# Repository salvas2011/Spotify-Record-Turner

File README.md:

#  RFID Record Player — ESP32-S3

> A modern record player that uses RFID-tagged vinyl coasters to control Spotify playback, powered by an ESP32-S3 and a custom PCB.

---

## How it works

Place a tagged vinyl coaster on the platter. The RFID reader identifies the tag, looks up the mapped Spotify URI, and starts playback. A Hall effect sensor detects when the platter is spinning — remove the record and the music pauses automatically. A stepper motor keeps the platter spinning for the full vinyl experience.

---

## PCB

<p align="center">
  
  &nbsp;
  
</p>

<p align="center">
  <em>Left: KiCad schematic &nbsp;·&nbsp; Right: PCB layout</em>
</p>

---

## Components

| Component | Purpose |
|---|---|
| ESP32-S3-DEV-KIT-N8R8 | Main microcontroller, Wi-Fi |
| RC522 RFID Reader | Reads RFID/NFC tags |
| 28BYJ-48 + ULN2003 | Stepper motor for spinning platter |
| A3144 Hall Effect Sensor | Detects platter rotation |
| NTAG213 NFC Tags | Attached to vinyl coasters |

---

## Wiring

### RC522 RFID (SPI)

| ESP32 GPIO | RC522 Pin |
|---|---|
| GPIO11 | MOSI |
| GPIO13 | MISO |
| GPIO12 | SCK |
| GPIO10 | CS (SDA) |
| GPIO9 | RST |
| 3.3V | 3.3V |
| GND | GND |

### ULN2003 Stepper Motor

| ESP32 GPIO | ULN2003 Pin |
|---|---|
| GPIO4 | IN1 |
| GPIO5 | IN2 |
| GPIO6 | IN3 |
| GPIO7 | IN4 |
| 5V (external) | VCC |
| GND | GND |

### A3144 Hall Effect Sensor

| ESP32 GPIO | Sensor Pin |
|---|---|
| GPIO38 | OUT |
| 3.3V | VCC |
| GND | GND |

### Power

5V 2A via barrel jack wired directly to the ESP32-S3 5V and GND pins.

---

## Pin notes

- GPIO35, 36, 37 are reserved internally on the N8R8 variant (Octal PSRAM) — do not use
- GPIO0 and GPIO46 are strapping pins — avoid for general use
- GPIO19/20 are USB D-/D+ — avoid if using native USB

---

## License

MIT

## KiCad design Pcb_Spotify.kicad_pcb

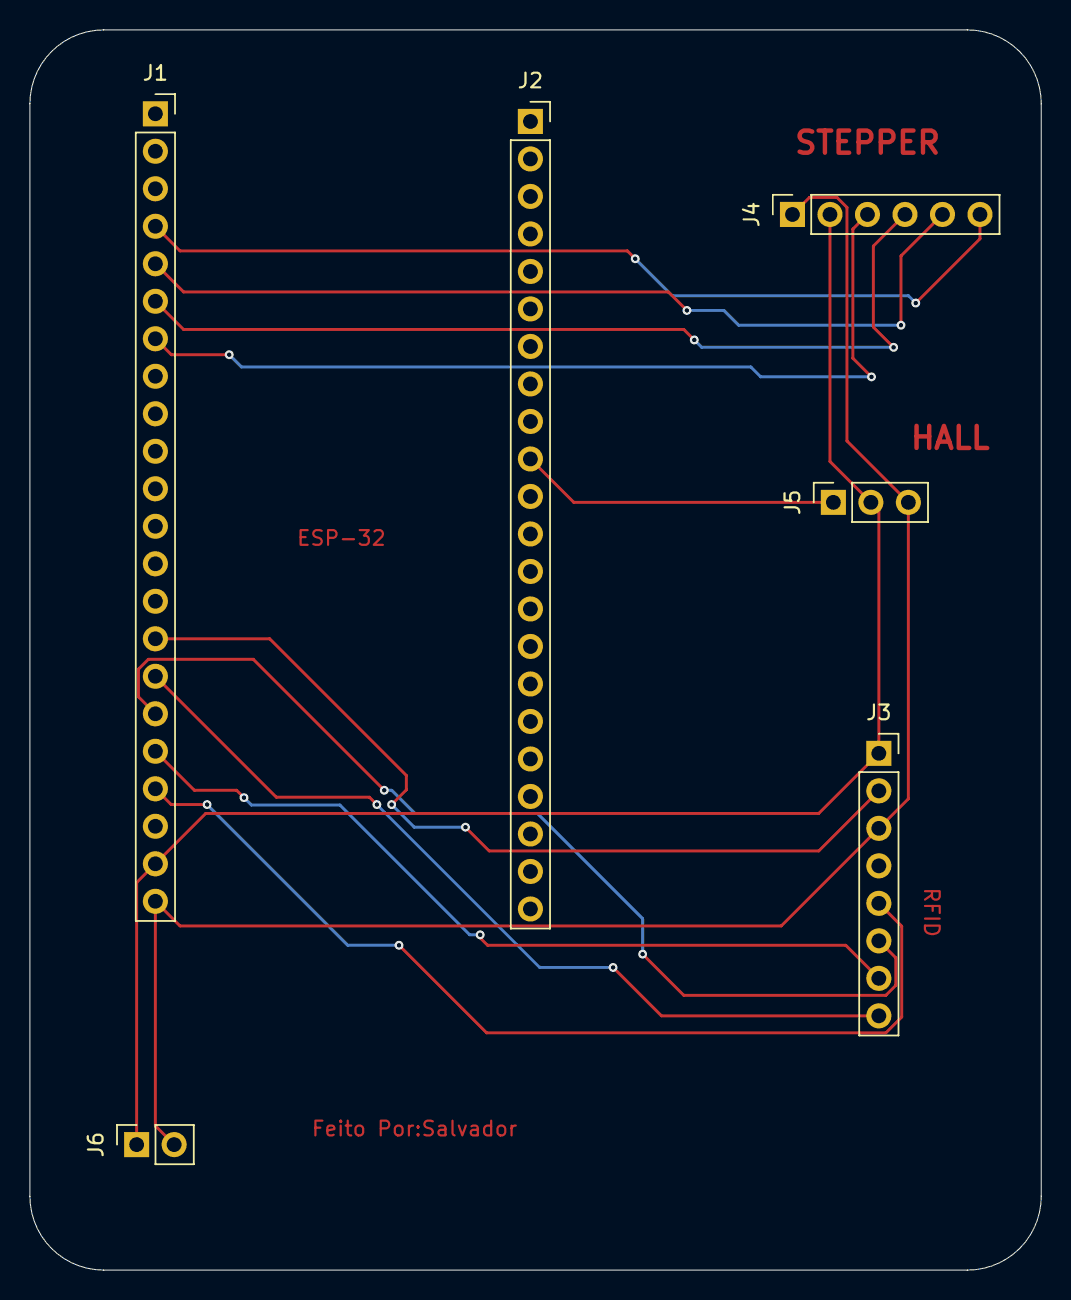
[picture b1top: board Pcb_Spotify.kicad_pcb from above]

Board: 2 copper layers, 68.5 x 84.0 mm, 6 parts (0 on the bottom side), 12 nets.

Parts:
J1, J2: Conn_01x22; PinSocket_1x22_P2.54mm_Vertical
J3: Conn_01x08; PinSocket_1x08_P2.54mm_Vertical
J4: Stepper; PinSocket_1x06_P2.54mm_Vertical
J5: Hall; PinSocket_1x03_P2.54mm_Vertical
J6: Input; PinSocket_1x02_P2.54mm_Vertical

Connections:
+5V: J1.21, J3.1, J4.2, J5.2, J6.1
GND: J1.22, J3.3, J4.1, J5.3, J6.2
unnamed: J1.4, J4.6
unnamed: J1.5, J4.5
unnamed: J1.6, J4.4
unnamed: J1.7, J4.3
unnamed: J1.15, J3.2
unnamed: J1.16, J3.8
unnamed: J1.17, J3.6
unnamed: J1.18, J3.7
unnamed: J1.19, J3.5
unnamed: J2.10 (Pin_10_10), J5.1

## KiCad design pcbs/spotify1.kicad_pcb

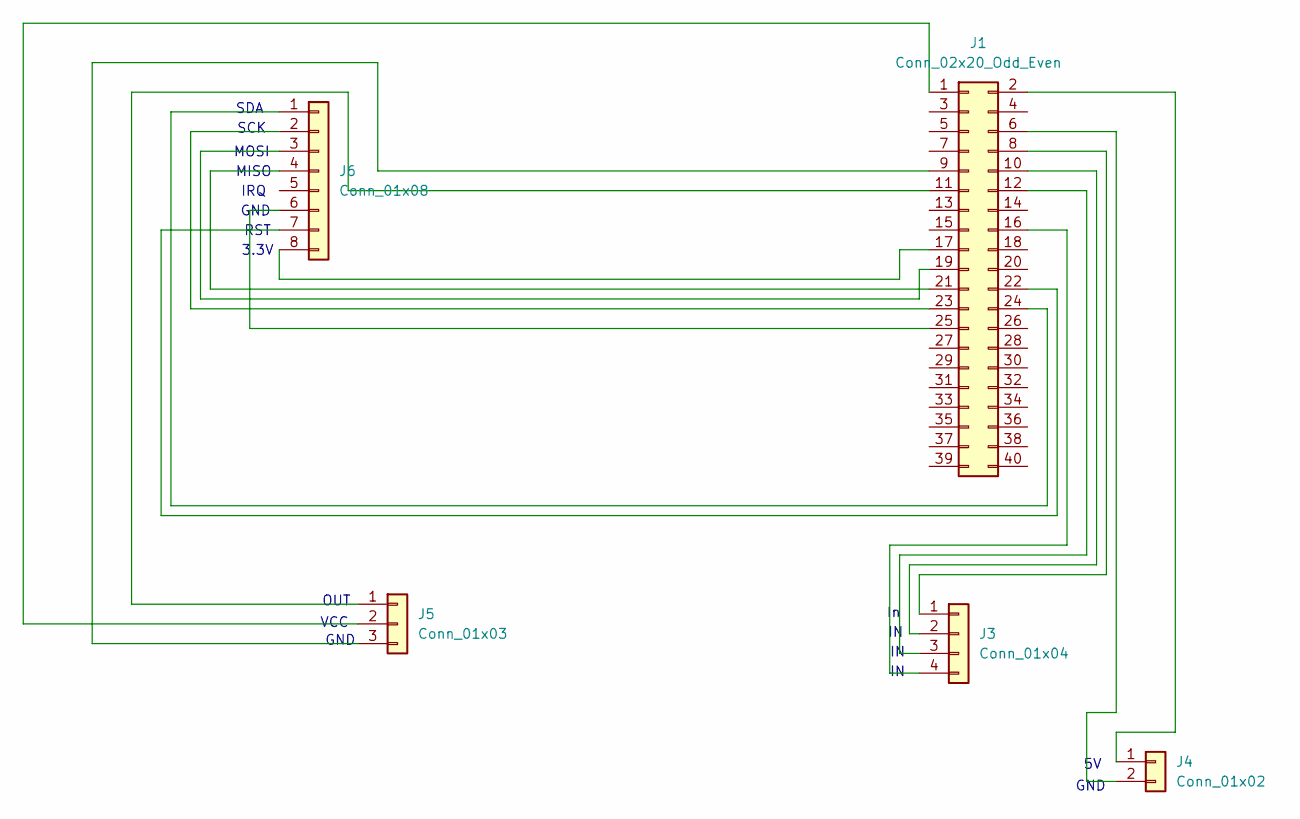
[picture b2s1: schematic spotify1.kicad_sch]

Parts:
J1: Conn_02x20_Odd_Even; PinSocket_2x20_P2.54mm_Vertical
J3: Conn_01x04; PinSocket_1x04_P2.54mm_Vertical
J4: Conn_01x02; PinSocket_1x02_P2.54mm_Vertical
J5: Conn_01x03; PinSocket_1x03_P2.54mm_Vertical
J6: Conn_01x08; PinSocket_1x08_P2.54mm_Vertical

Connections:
unnamed: J1.1, J5.2
unnamed: J1.2, J4.1
unnamed: J1.6, J4.2
unnamed: J1.8, J3.1
unnamed: J1.9, J5.3
unnamed: J1.10, J3.2
unnamed: J1.11, J5.1
unnamed: J1.12, J3.3
unnamed: J1.16, J3.4
unnamed: J1.17, J6.8
unnamed: J1.19, J6.3
unnamed: J1.21, J6.4
unnamed: J1.22, J6.7
unnamed: J1.23, J6.2
unnamed: J1.24, J6.1
unnamed: J1.25, J6.6

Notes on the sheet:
3.3V
IRQ
MISO
SCK
RST
MOSI
SDA
GND
VCC
OUT

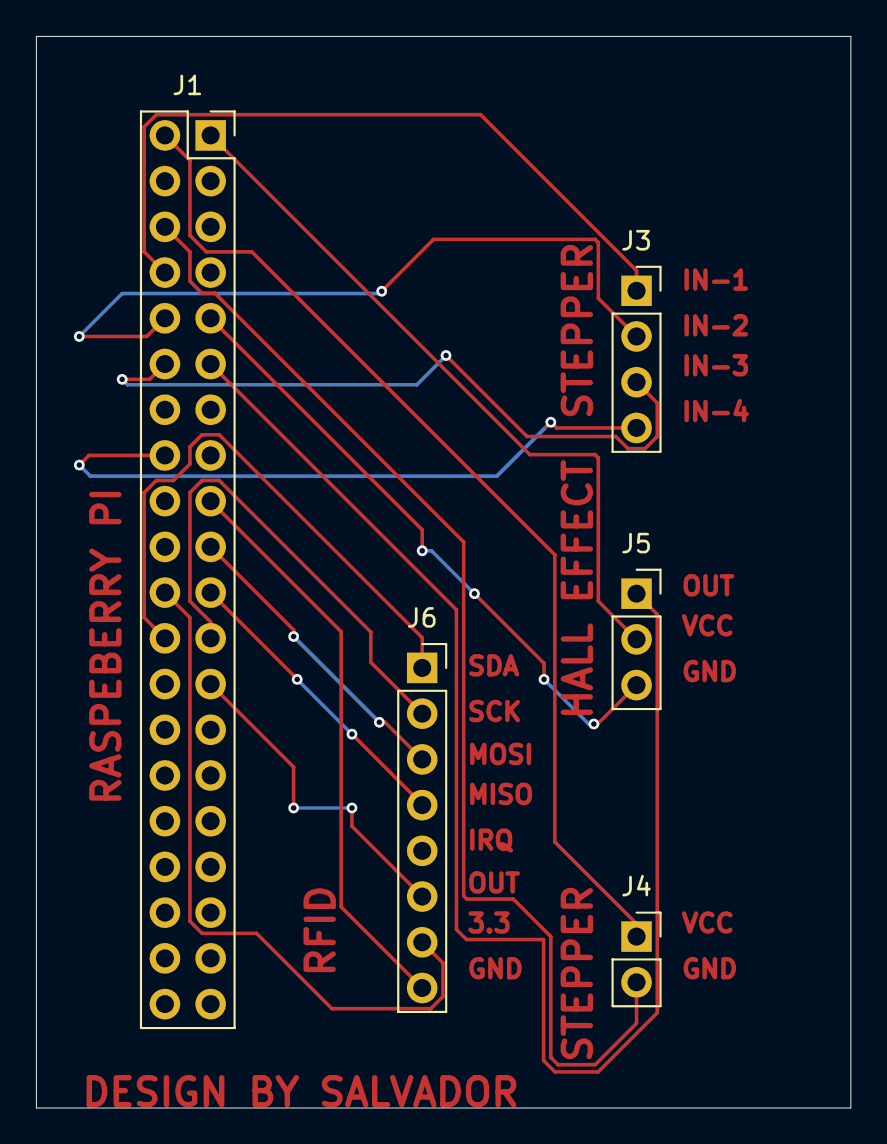
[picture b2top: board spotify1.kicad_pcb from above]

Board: 2 copper layers, 45.2 x 59.5 mm, 5 parts (0 on the bottom side), 16 nets.

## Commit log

2026-02-20 Revise README for clarity and project details
    Expanded project description and added details about hardware redesign, compatibility, and components.
2026-03-05 Add Bill of Materials section to README
    Added a Bill of Materials (BOM) section detailing components and their quantities for the project.
2026-03-05 add pcb
2026-03-07 Revise README for ESP32-S3 implementation
    Updated README to reflect transition from Raspberry Pi to ESP32-S3, including hardware and software changes.
2026-06-03 readme
